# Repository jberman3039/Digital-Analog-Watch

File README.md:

# Digital-Analog-Watch
The "Digital Analog Watch" is an ATTiny85-based project that displays hours and minutes using and outer and inner rings of LEDs respectively. The project includes a custom drivers to set and get the time for an D3231 RTC via I2C communication and update the LEDs on the PCB with 74HC595 shift registers. To initially set the time on the RTC, uncomment "#define SET_TIME" in main.c and set the values for HOUR, MINUTE, and SECOND. After initially flashing and running the code, this line must be recommented out and the code reflashed. The RTC will continue to keep accurate time as long as VBAT is connected to a power source such as a CR2032 coin cell battery. To flash the code to the ATTiny85, navigate to the src folder and run the command "make flash". This project was inspired by https://github.com/brunob45/watch/tree/master.

# PCB
The PCB was designed in KiCad 9.0.

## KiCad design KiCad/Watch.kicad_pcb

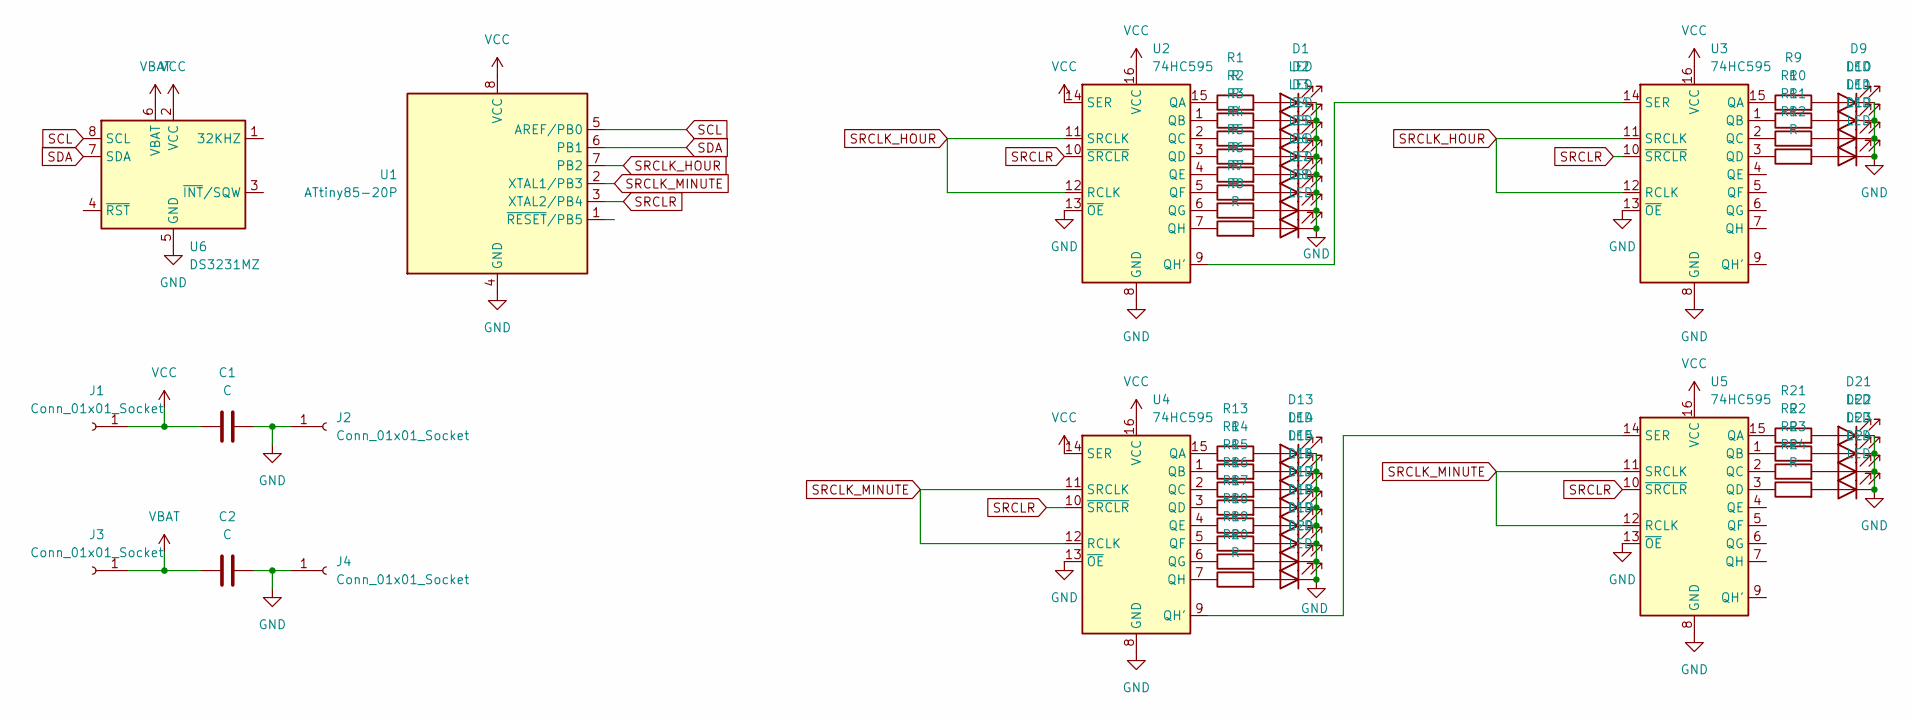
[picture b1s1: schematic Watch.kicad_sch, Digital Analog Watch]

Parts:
C1, C2: C; C_0805_2012Metric_Pad1.18x1.45mm_HandSolder
D1, D2, D3, D4, D5, D6, D7, D8, D9, D10, D11, D12, D13, D14, D15, D16, D17, D18, D19, D20, D21, D22, D23, D24: LED; LED_0805_2012Metric_Pad1.15x1.40mm_HandSolder
J1, J2, J3, J4: Conn_01x01_Socket; SolderWire-0.75sqmm_1x01_D1.25mm_OD2.3mm
R1, R2, R3, R4, R5, R6, R7, R8, R9, R10, R11, R12, R13, R14, R15, R16, R17, R18, R19, R20, R21, R22, R23, R24: R; R_0805_2012Metric_Pad1.20x1.40mm_HandSolder
U1: ATtiny85-20P; DIP-8_W7.62mm_Socket
U2, U3, U4, U5: 74HC595; SOIC-16_3.9x9.9mm_P1.27mm
U6: DS3231MZ; SOIC-8_3.9x4.9mm_P1.27mm

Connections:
GND: C1.2, C2.2, D1.1 (K), D2.1 (K), D3.1 (K), D4.1 (K), D5.1 (K), D6.1 (K), D7.1 (K), D8.1 (K), D9.1 (K), D10.1 (K), D11.1 (K), D12.1 (K), D13.1 (K), D14.1 (K), D15.1 (K), D16.1 (K), D17.1 (K), D18.1 (K), D19.1 (K), D20.1 (K), D21.1 (K), D22.1 (K), D23.1 (K), D24.1 (K), J2.1, J4.1, U1.4 (GND), U2.8 (GND), U2.13 (~OE), U3.8 (GND), U3.13 (~OE), U4.8 (GND), U4.13 (~OE), U5.8 (GND), U5.13 (~OE), U6.5 (GND)
unnamed: D1.2 (A), R1.2
unnamed: D2.2 (A), R2.2
unnamed: D3.2 (A), R3.2
unnamed: D4.2 (A), R4.2
unnamed: D5.2 (A), R5.2
unnamed: D6.2 (A), R6.2
unnamed: D7.2 (A), R7.2
unnamed: D8.2 (A), R8.2
unnamed: D9.2 (A), R9.2
unnamed: D10.2 (A), R10.2
unnamed: D11.2 (A), R11.2
unnamed: D12.2 (A), R12.2
unnamed: D13.2 (A), R13.2
unnamed: D14.2 (A), R14.2
unnamed: D15.2 (A), R15.2
unnamed: D16.2 (A), R16.2
unnamed: D17.2 (A), R17.2
unnamed: D18.2 (A), R18.2
unnamed: D19.2 (A), R19.2
unnamed: D20.2 (A), R20.2
unnamed: D21.2 (A), R21.2
unnamed: D22.2 (A), R22.2
unnamed: D23.2 (A), R23.2
unnamed: D24.2 (A), R24.2
unnamed: R1.1, U2.15 (QA)
unnamed: R2.1, U2.1 (QB)
unnamed: R3.1, U2.2 (QC)
unnamed: R4.1, U2.3 (QD)
unnamed: R5.1, U2.4 (QE)
unnamed: R6.1, U2.5 (QF)
unnamed: R7.1, U2.6 (QG)
unnamed: U2.9 (QH'), U3.14 (SER)
unnamed: R8.1, U2.7 (QH)
unnamed: R9.1, U3.15 (QA)
unnamed: R10.1, U3.1 (QB)
unnamed: R11.1, U3.2 (QC)
unnamed: R12.1, U3.3 (QD)
unnamed: R13.1, U4.15 (QA)
unnamed: R14.1, U4.1 (QB)
unnamed: R15.1, U4.2 (QC)
unnamed: R16.1, U4.3 (QD)
unnamed: R17.1, U4.4 (QE)
unnamed: R18.1, U4.5 (QF)
unnamed: R19.1, U4.6 (QG)
unnamed: U4.9 (QH'), U5.14 (SER)
unnamed: R20.1, U4.7 (QH)
unnamed: R21.1, U5.15 (QA)
unnamed: R22.1, U5.1 (QB)
unnamed: R23.1, U5.2 (QC)
unnamed: R24.1, U5.3 (QD)
SCL: U1.5 (AREF/PB0), U6.8 (SCL)
SDA: U1.6 (PB1), U6.7 (SDA)
SRCLK_HOUR: U1.7 (PB2), U2.11 (SRCLK), U2.12 (RCLK), U3.11 (SRCLK), U3.12 (RCLK)
SRCLK_MINUTE: U1.2 (XTAL1/PB3), U4.11 (SRCLK), U4.12 (RCLK), U5.11 (SRCLK), U5.12 (RCLK)
SRCLR: U1.3 (XTAL2/PB4), U2.10 (~SRCLR), U3.10 (~SRCLR), U4.10 (~SRCLR), U5.10 (~SRCLR)
VBAT: C2.1, J3.1, U6.6 (VBAT)
VCC: C1.1, J1.1, U1.8 (VCC), U2.14 (SER), U2.16 (VCC), U3.16 (VCC), U4.14 (SER), U4.16 (VCC), U5.16 (VCC), U6.2 (VCC)

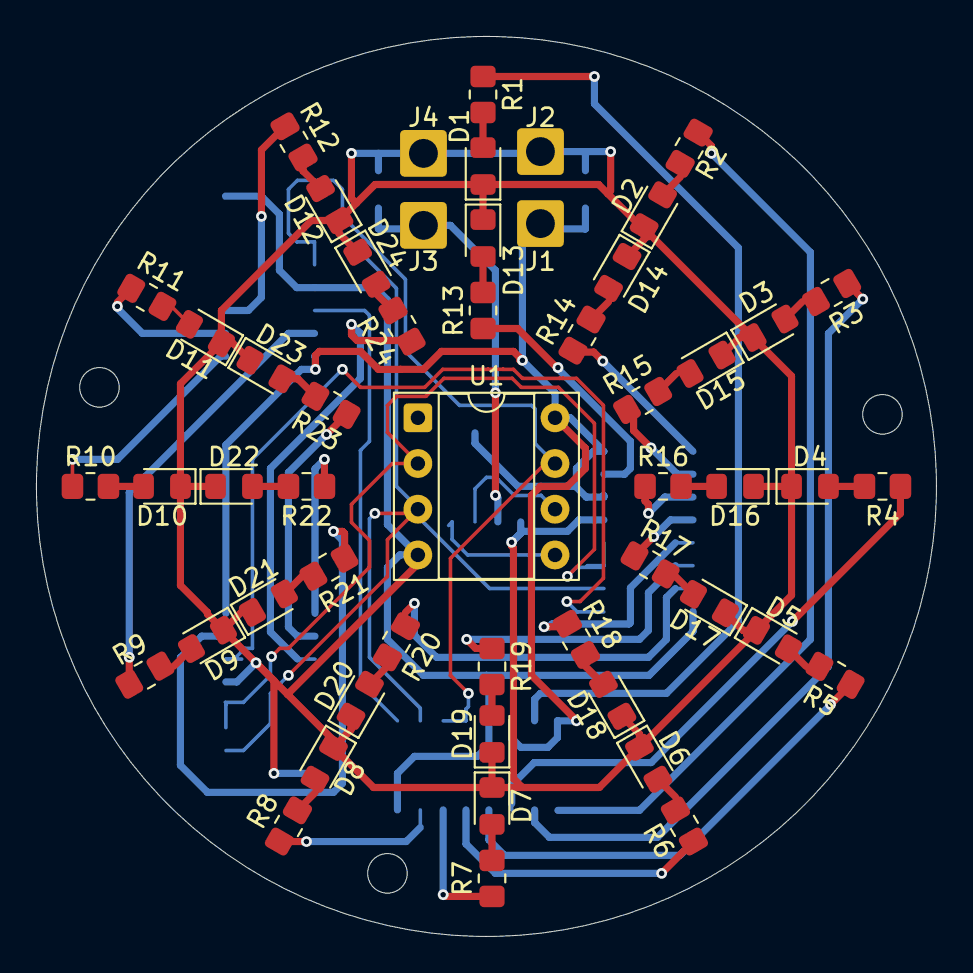
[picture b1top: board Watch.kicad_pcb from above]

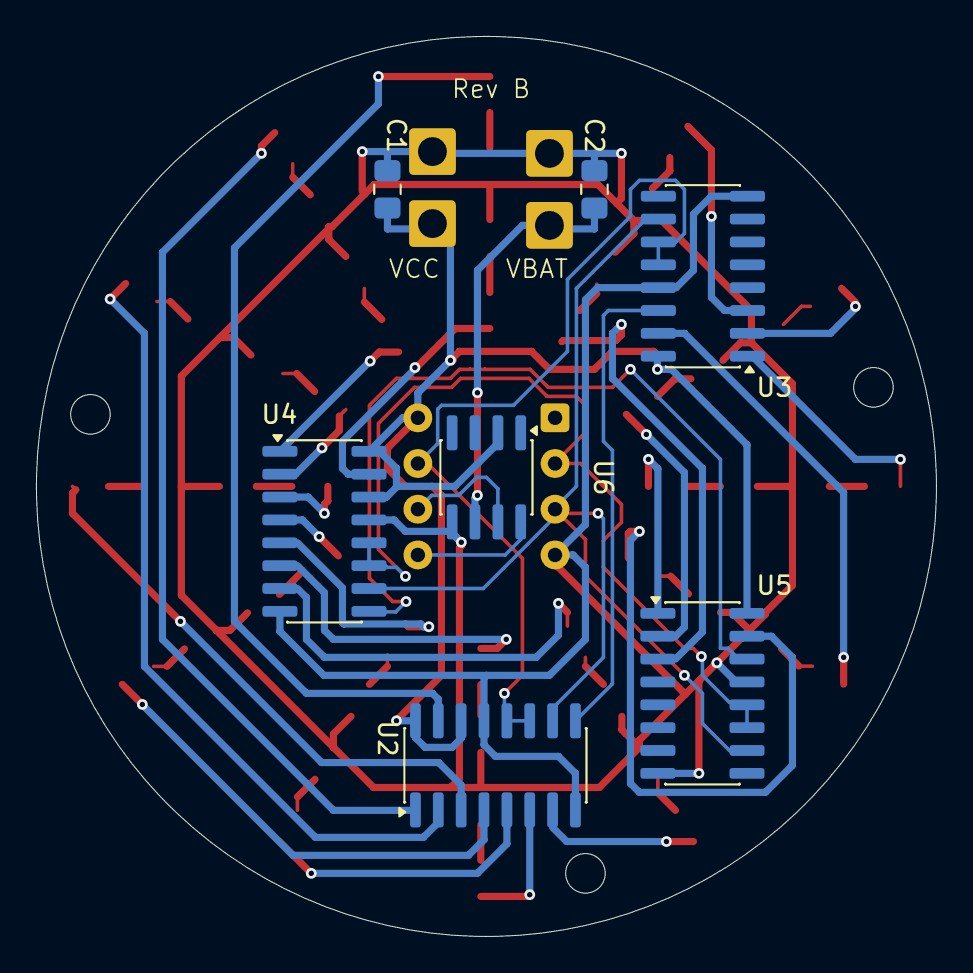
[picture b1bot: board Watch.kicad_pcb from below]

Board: 2 copper layers, 50.0 x 50.0 mm, 63 parts (7 on the bottom side), 58 nets.

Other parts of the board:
 : MountingHole_2.2mm_M2
 #2,  #3: MountingHole_2.2mm_M2

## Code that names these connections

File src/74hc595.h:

#define SRCLK_HOUR_PIN 2 // PB2
#define SRCLK_MINUTE_PIN 3 // PB3
#define SRCLR_PIN 4 // PB4

void init_74hc595();
void clear_sr();
void update_hour(unsigned char* rtc_hour);
void update_minute(unsigned char* rtc_minute);
void update_time(unsigned char* rtc_hour, unsigned char* rtc_minute);

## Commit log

2025-11-16 adding image folder
